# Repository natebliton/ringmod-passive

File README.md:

# ringmod-passive
This is a KiCAD implementation of a passive ring modulator using two 42TM018-RC transformers, in a eurorack package.

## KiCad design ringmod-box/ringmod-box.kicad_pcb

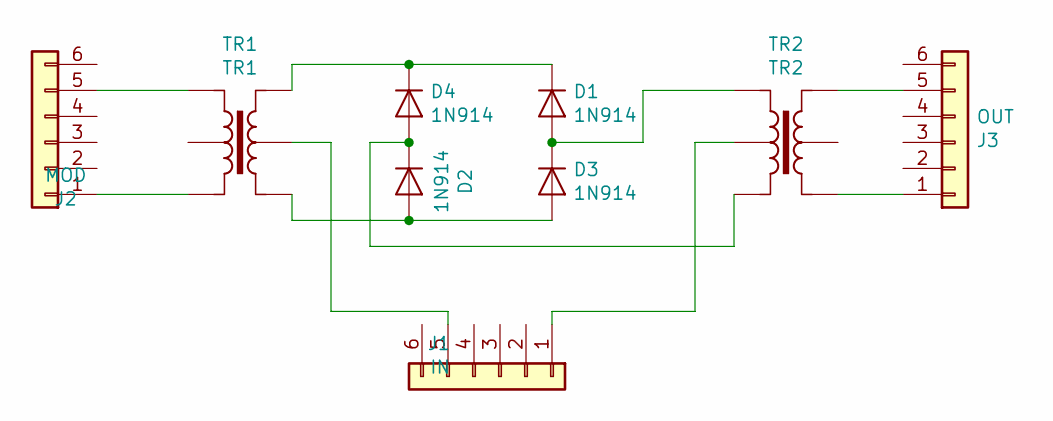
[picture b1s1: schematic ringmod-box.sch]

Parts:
D1, D2, D3, D4: 1N914; D_DO-35_SOD27_P7.62mm_Horizontal
J1: IN; StereoJackTRS3
J2: MOD; StereoJackTRS3
J3: OUT; StereoJackTRS3
TR1: TR1; TM018-R Transformer
TR2: TR2; TM018-R Transformer

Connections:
unnamed: D1.1 (K), D4.1 (K), TR1.6
unnamed: D1.2 (A), D3.1 (K), TR2.1
unnamed: D2.1 (K), D4.2 (A), TR2.3
unnamed: D2.2 (A), D3.2 (A), TR1.4
unnamed: J1.1, TR2.2
unnamed: J1.5, TR1.5
unnamed: J2.1, TR1.3
unnamed: J2.5, TR1.1
unnamed: J3.1, TR2.4
unnamed: J3.5, TR2.6

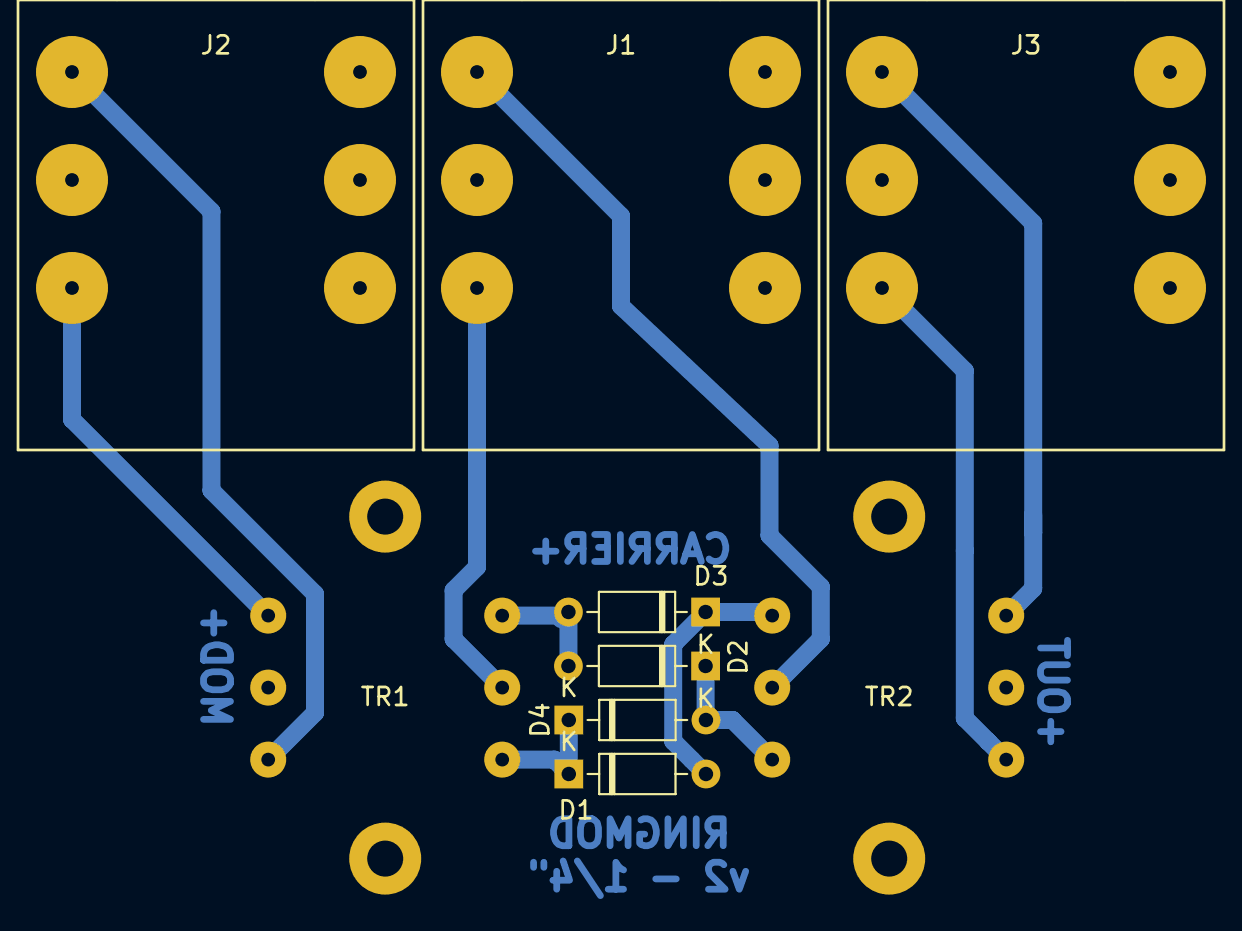
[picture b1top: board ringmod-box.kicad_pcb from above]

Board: 2 copper layers, 9 parts (0 on the bottom side), 10 nets.

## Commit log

2020-12-10 initial schematic and transformer footprint
2020-12-11 initial PCB layout
2020-12-14 added version with guitar jacks
